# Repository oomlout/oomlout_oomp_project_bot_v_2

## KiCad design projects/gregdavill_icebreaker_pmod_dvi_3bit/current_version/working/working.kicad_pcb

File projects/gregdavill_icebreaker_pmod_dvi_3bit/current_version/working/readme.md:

# icebreaker_pmod
 
## summary 
* id: gregdavill_icebreaker_pmod_dvi_3bit
* user: gregdavill
* name: icebreaker_pmod
* board: dvi_3bit
* repo: https://github.com/gregdavill/icebreaker-pmod
* src_file_repo_kicad_pcb: dvi-3bit/v1.0a/dvi-3bit.kicad_pcb
* src_file_repo_kicad_pcb_link: https://github.com/gregdavill/icebreaker-pmod/tree/master/dvi-3bit/v1.0a/dvi-3bit.kicad_pcb

* src_file_repo_sch: dvi-3bit/v1.0a/dvi-3bit.sch
* src_file_repo_sch_link: https://github.com/gregdavill/icebreaker-pmod/tree/master/dvi-3bit/v1.0a/dvi-3bit.sch
* full details link: https://github.com/oomlout/oomlout_oomp_project_bot_v_2/tree/main/projects/gregdavill_icebreaker_pmod_dvi_3bit/current_version/working

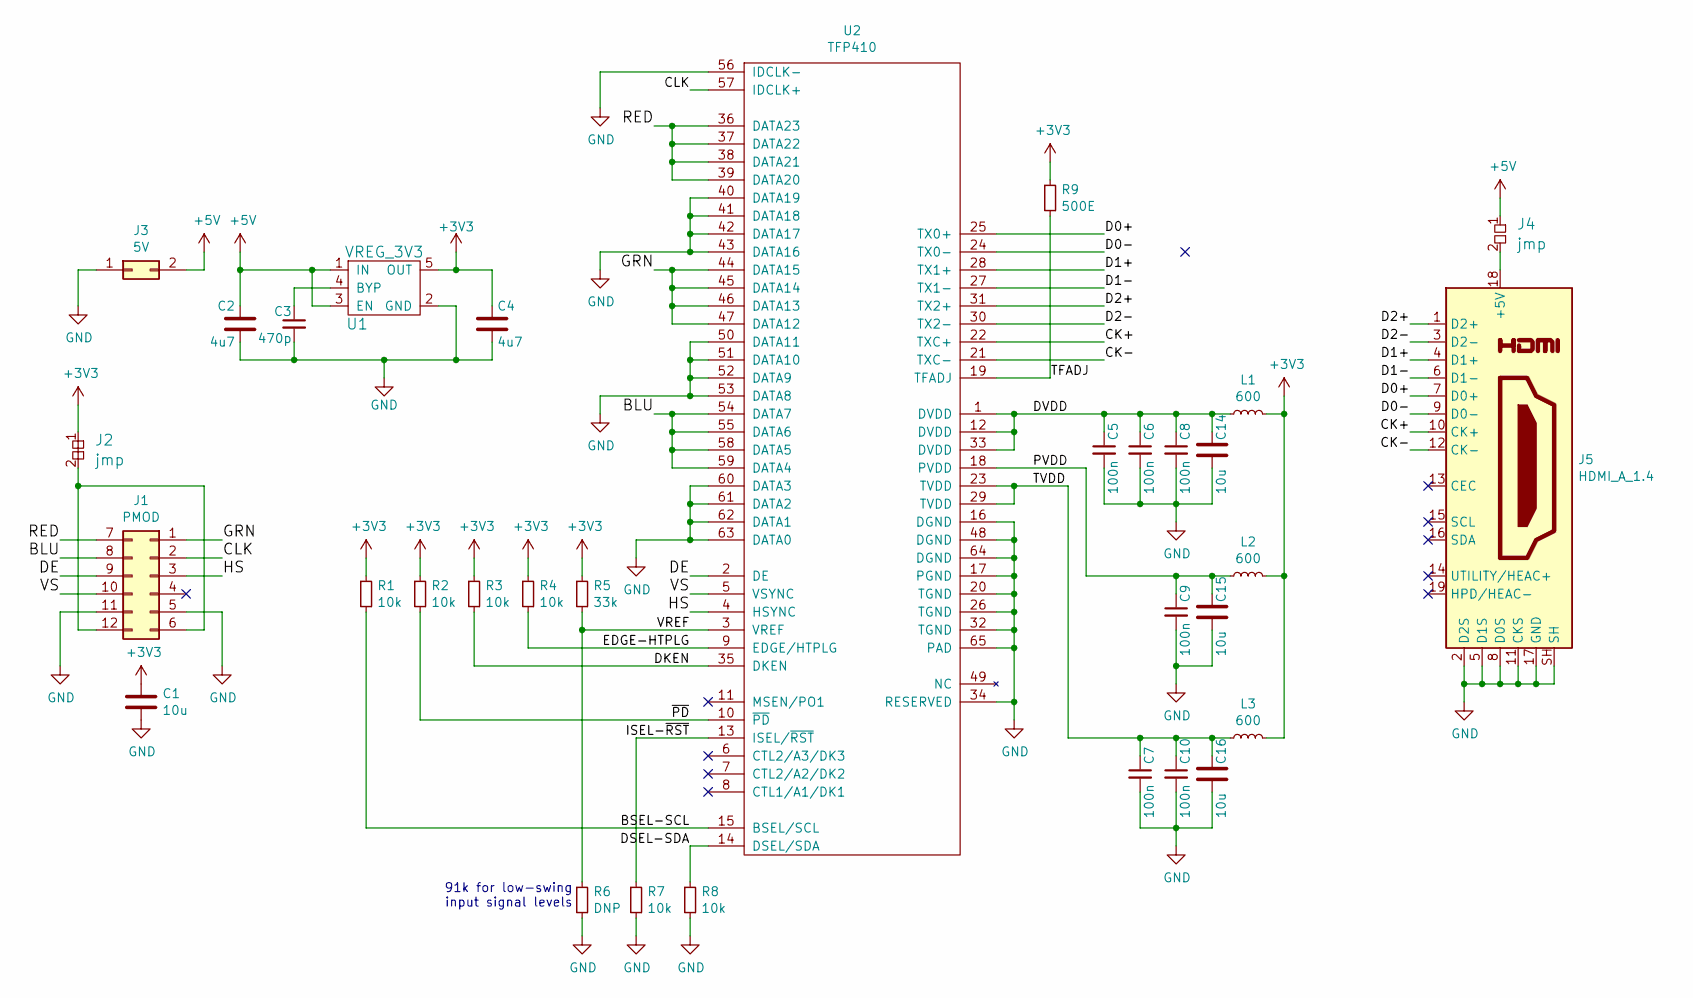
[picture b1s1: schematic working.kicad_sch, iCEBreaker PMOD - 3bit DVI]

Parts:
C1, C14, C15, C16: 10u; C_0603
C2, C4: 4u7; C_0603
C3: 470p; C_0402
C5, C6, C7, C8, C9, C10: 100n; C_0402
J1: PMOD; PMODHeader_2x06_P2.54mm_Horizontal
J2: jmp; J_NC_0603_30
J3: 5V; PinHeader_2x01_P2.54mm_Vertical
J4: jmp; J_0603
J5: HDMI_A_1.4; HDMI-10029449-111RLF
L1, L2, L3: 600; L_0402
R1, R2, R3, R4, R7, R8: 10k; R_0402
R5: 33k; R_0402
R6: DNP; R_0402
R9: 500E; R_0402
U1: VREG_3V3; SOT-23-5
U2: TFP410; TQFP-64-1EP_10x10mm_P0.5mm_EP5x5mm

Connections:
+3V3: C1.1, C4.1, J2.1, L1.1, L2.1, L3.1, R1.1, R2.1, R3.1, R4.1, R5.1, R9.1, U1.5 (OUT)
+5V: C2.1, J3.2, J4.1, U1.1 (IN), U1.3 (EN)
/BLU: J1.8, U2.54 (DATA7), U2.55 (DATA6), U2.58 (DATA5), U2.59 (DATA4)
/BSEL-SCL: R1.2, U2.15 (BSEL/SCL)
/CK+: J5.10 (CK+), U2.22 (TXC+)
/CK-: J5.12 (CK-), U2.21 (TXC-)
/CLK: J1.2, U2.57 (IDCLK+)
/D0+: J5.7 (D0+), U2.25 (TX0+)
/D0-: J5.9 (D0-), U2.24 (TX0-)
/D1+: J5.4 (D1+), U2.28 (TX1+)
/D1-: J5.6 (D1-), U2.27 (TX1-)
/D2+: J5.1 (D2+), U2.31 (TX2+)
/D2-: J5.3 (D2-), U2.30 (TX2-)
/DE: J1.9, U2.2 (DE)
/DKEN: R3.2, U2.35 (DKEN)
/DSEL-SDA: R8.1, U2.14 (DSEL/SDA)
/DVDD: C5.1, C6.1, C8.1, C14.1, L1.2, U2.1 (DVDD), U2.12 (DVDD), U2.33 (DVDD)
/EDGE-HTPLG: R4.2, U2.9 (EDGE/HTPLG)
/GRN: J1.1, U2.44 (DATA15), U2.45 (DATA14), U2.46 (DATA13), U2.47 (DATA12)
/HS: J1.3, U2.4 (HSYNC)
/ISEL-~RST: R7.1, U2.13 (ISEL/~RST)
/PVDD: C9.1, C15.1, L2.2, U2.18 (PVDD)
/RED: J1.7, U2.36 (DATA23), U2.37 (DATA22), U2.38 (DATA21), U2.39 (DATA20)
/TFADJ: R9.2, U2.19 (TFADJ)
/TVDD: C7.1, C10.1, C16.1, L3.2, U2.23 (TVDD), U2.29 (TVDD)
/VREF: R5.2, R6.1, U2.3 (VREF)
/VS: J1.10, U2.5 (VSYNC)
/~PD: R2.2, U2.10 (~PD)
GND: C1.2, C2.2, C3.2, C4.2, C5.2, C6.2, C7.2, C8.2, C9.2, C10.2, C14.2, C15.2, C16.2, J1.5, J1.11, J3.1, J5.2 (D2S), J5.5 (D1S), J5.8 (D0S), J5.11 (CKS), J5.17 (GND), J5.SH, R6.2, R7.2, R8.2, U1.2 (GND), U2.16 (DGND), U2.17 (PGND), U2.20 (TGND), U2.26 (TGND), U2.32 (TGND), U2.34 (RESERVED), U2.40 (DATA19), U2.41 (DATA18), U2.42 (DATA17), U2.43 (DATA16), U2.48 (DGND), U2.50 (DATA11), U2.51 (DATA10), U2.52 (DATA9), U2.53 (DATA8), U2.56 (IDCLK-), U2.60 (DATA3), U2.61 (DATA2), U2.62 (DATA1), U2.63 (DATA0), U2.64 (DGND), U2.65 (PAD)
unnamed: C3.1, U1.4 (BYP)
unnamed: J1.6, J1.12, J2.2
unnamed: J4.2, J5.18 (+5V)

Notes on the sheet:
91k for low-swing input signal levels

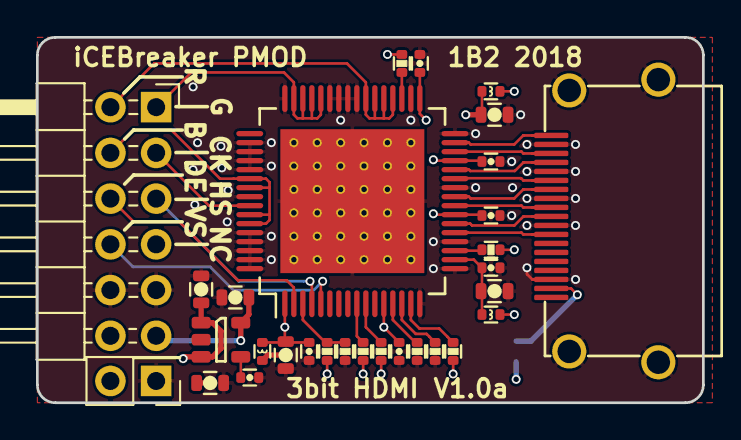
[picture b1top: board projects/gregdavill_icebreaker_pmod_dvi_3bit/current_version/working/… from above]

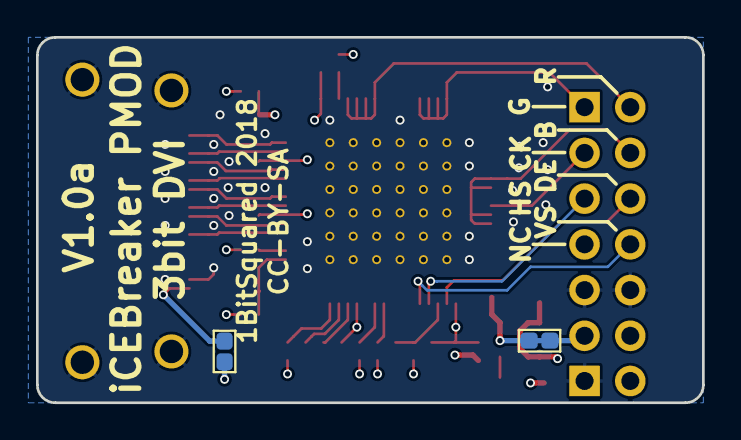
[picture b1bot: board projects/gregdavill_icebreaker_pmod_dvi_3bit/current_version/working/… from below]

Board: 4 copper layers, 37.0 x 20.3 mm, 32 parts (2 on the bottom side), 32 nets.

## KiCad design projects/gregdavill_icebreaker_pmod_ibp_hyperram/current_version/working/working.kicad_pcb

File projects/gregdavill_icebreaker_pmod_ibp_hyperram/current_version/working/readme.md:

# icebreaker_pmod
 
## summary 
* id: gregdavill_icebreaker_pmod_ibp_hyperram
* user: gregdavill
* name: icebreaker_pmod
* board: ibp_hyperram
* repo: https://github.com/gregdavill/icebreaker-pmod
* src_file_repo_kicad_pcb: hyperram/v1.0b/ibp-hyperram.kicad_pcb
* src_file_repo_kicad_pcb_link: https://github.com/gregdavill/icebreaker-pmod/tree/master/hyperram/v1.0b/ibp-hyperram.kicad_pcb

* src_file_repo_sch: hyperram/v1.0b/ibp-hyperram.sch
* src_file_repo_sch_link: https://github.com/gregdavill/icebreaker-pmod/tree/master/hyperram/v1.0b/ibp-hyperram.sch
* full details link: https://github.com/oomlout/oomlout_oomp_project_bot_v_2/tree/main/projects/gregdavill_icebreaker_pmod_ibp_hyperram/current_version/working

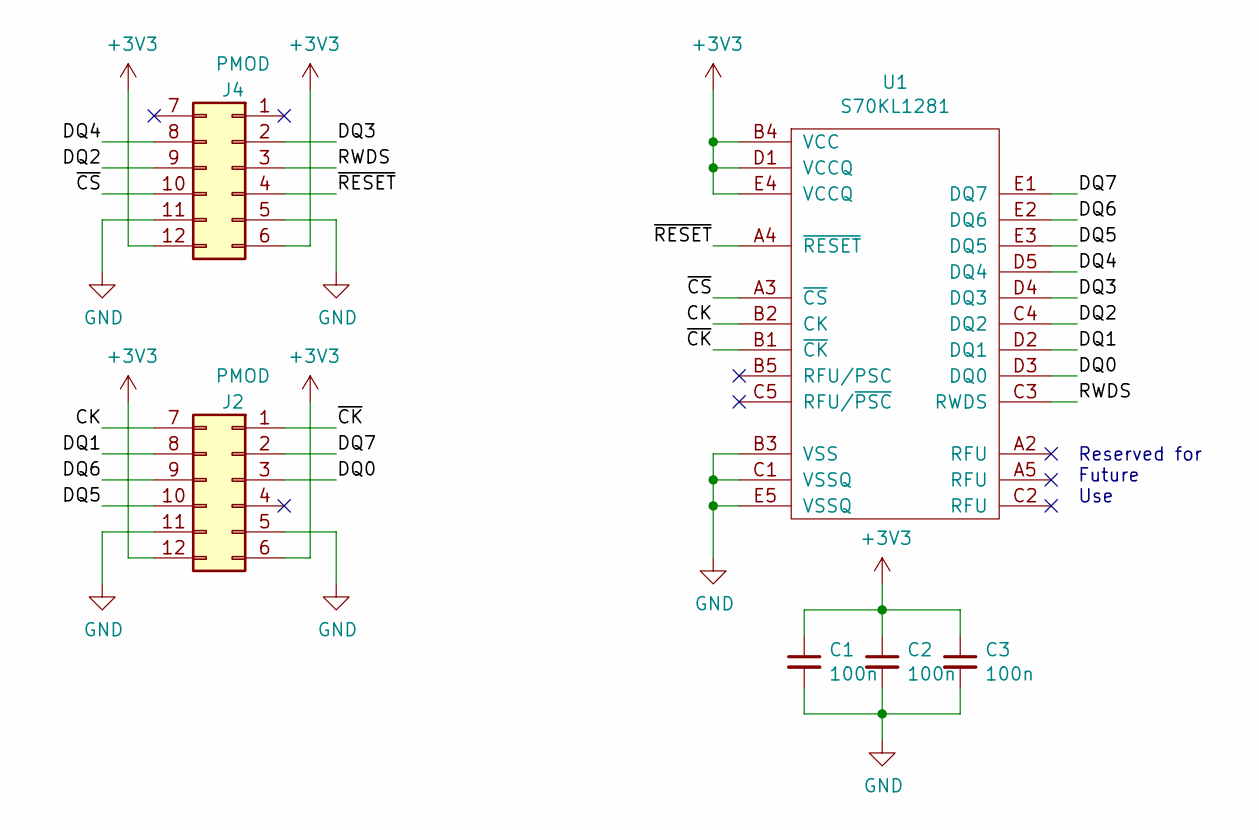
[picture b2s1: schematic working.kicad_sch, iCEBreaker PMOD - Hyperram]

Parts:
C1, C2, C3: 100n; C_0402
J2, J4: PMOD; PMODHeader_2x06_P2.54mm_Horizontal
U1: S70KL1281; BGA-24_5x5_6.0x8.0mm

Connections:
+3V3: C1.1, C2.1, C3.1, J2.6, J2.12, J4.6, J4.12, U1.B4 (VCC), U1.D1 (VCCQ), U1.E4 (VCCQ)
/CK: J2.7, U1.B2 (CK)
/DQ0: J2.3, U1.D3 (DQ0)
/DQ1: J2.8, U1.D2 (DQ1)
/DQ2: J4.9, U1.C4 (DQ2)
/DQ3: J4.2, U1.D4 (DQ3)
/DQ4: J4.8, U1.D5 (DQ4)
/DQ5: J2.10, U1.E3 (DQ5)
/DQ6: J2.9, U1.E2 (DQ6)
/DQ7: J2.2, U1.E1 (DQ7)
/RWDS: J4.3, U1.C3 (RWDS)
/~CK: J2.1, U1.B1 (~CK)
/~CS: J4.10, U1.A3 (~CS)
/~RESET: J4.4, U1.A4 (~RESET)
GND: C1.2, C2.2, C3.2, J2.5, J2.11, J4.5, J4.11, U1.B3 (VSS), U1.C1 (VSSQ), U1.E5 (VSSQ)

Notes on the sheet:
Reserved for Future Use

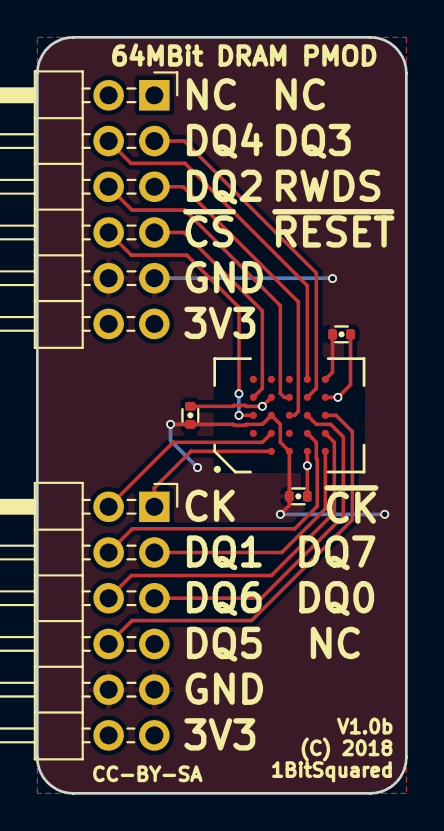
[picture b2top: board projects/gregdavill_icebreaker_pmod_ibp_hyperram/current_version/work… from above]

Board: 2 copper layers, 20.5 x 42.0 mm, 6 parts (0 on the bottom side), 15 nets.

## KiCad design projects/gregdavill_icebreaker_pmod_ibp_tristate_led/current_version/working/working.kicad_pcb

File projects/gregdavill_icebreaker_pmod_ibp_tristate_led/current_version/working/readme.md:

# icebreaker_pmod
 
## summary 
* id: gregdavill_icebreaker_pmod_ibp_tristate_led
* user: gregdavill
* name: icebreaker_pmod
* board: ibp_tristate_led
* repo: https://github.com/gregdavill/icebreaker-pmod
* src_file_repo_kicad_pcb: tristate-led/v1.0a/ibp-tristate-led.kicad_pcb
* src_file_repo_kicad_pcb_link: https://github.com/gregdavill/icebreaker-pmod/tree/master/tristate-led/v1.0a/ibp-tristate-led.kicad_pcb

* src_file_repo_sch: tristate-led/v1.0a/ibp-tristate-led.sch
* src_file_repo_sch_link: https://github.com/gregdavill/icebreaker-pmod/tree/master/tristate-led/v1.0a/ibp-tristate-led.sch
* full details link: https://github.com/oomlout/oomlout_oomp_project_bot_v_2/tree/main/projects/gregdavill_icebreaker_pmod_ibp_tristate_led/current_version/working

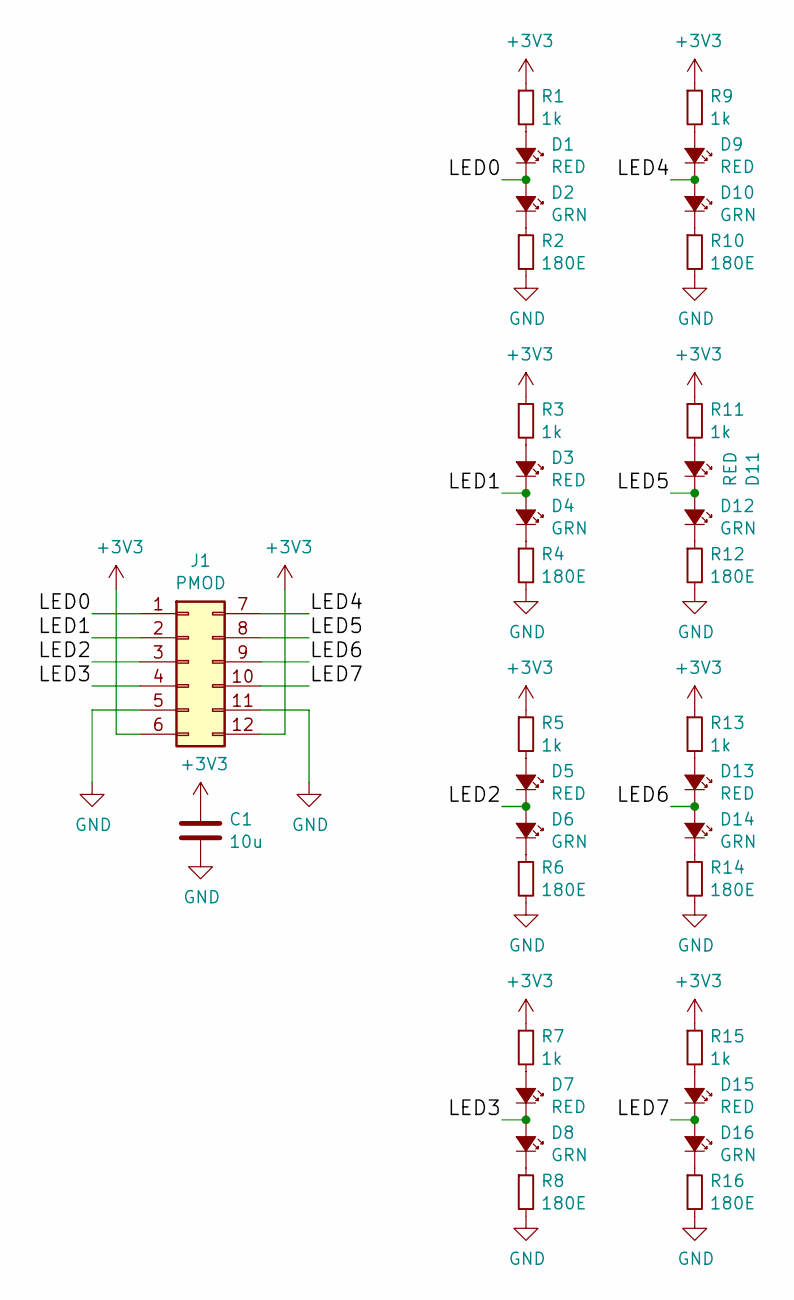
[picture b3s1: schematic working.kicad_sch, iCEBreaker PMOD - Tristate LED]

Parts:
C1: 10u; C_0603
D1, D3, D5, D7, D9, D11, D13, D15: RED; D_0603
D2, D4, D6, D8, D10, D12, D14, D16: GRN; D_0603
J1: PMOD; PMODHeader_2x06_P2.54mm_Horizontal
R1, R3, R5, R7, R9, R11, R13, R15: 1k; R_0402
R2, R4, R6, R8, R10, R12, R14, R16: 180E; R_0402

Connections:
+3V3: C1.1, J1.6, J1.12, R1.1, R3.1, R5.1, R7.1, R9.1, R11.1, R13.1, R15.1
/LED0: D1.C, D2.A, J1.1
/LED1: D3.C, D4.A, J1.2
/LED2: D5.C, D6.A, J1.3
/LED3: D7.C, D8.A, J1.4
/LED4: D9.C, D10.A, J1.7
/LED5: D11.C, D12.A, J1.8
/LED6: D13.C, D14.A, J1.9
/LED7: D15.C, D16.A, J1.10
GND: C1.2, J1.5, J1.11, R2.2, R4.2, R6.2, R8.2, R10.2, R12.2, R14.2, R16.2
unnamed: D1.A, R1.2
unnamed: D2.C, R2.1
unnamed: D3.A, R3.2
unnamed: D4.C, R4.1
unnamed: D5.A, R5.2
unnamed: D6.C, R6.1
unnamed: D7.A, R7.2
unnamed: D8.C, R8.1
unnamed: D9.A, R9.2
unnamed: D10.C, R10.1
unnamed: D11.A, R11.2
unnamed: D12.C, R12.1
unnamed: D13.A, R13.2
unnamed: D14.C, R14.1
unnamed: D15.A, R15.2
unnamed: D16.C, R16.1

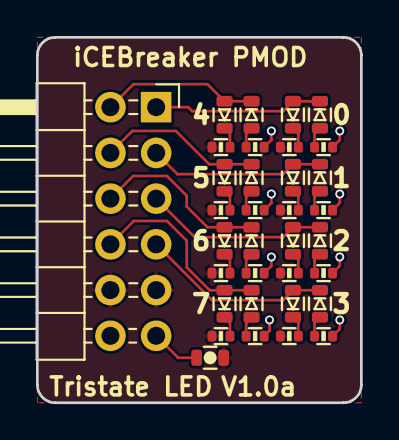
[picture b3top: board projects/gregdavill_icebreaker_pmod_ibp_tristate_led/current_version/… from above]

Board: 2 copper layers, 18.0 x 20.3 mm, 34 parts (0 on the bottom side), 26 nets.

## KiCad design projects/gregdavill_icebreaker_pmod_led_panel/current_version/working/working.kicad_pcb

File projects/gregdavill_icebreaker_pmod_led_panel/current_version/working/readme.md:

# icebreaker_pmod
 
## summary 
* id: gregdavill_icebreaker_pmod_led_panel
* user: gregdavill
* name: icebreaker_pmod
* board: led_panel
* repo: https://github.com/gregdavill/icebreaker-pmod
* src_file_repo_kicad_pcb: led-panel/v1.1a/led-panel.kicad_pcb
* src_file_repo_kicad_pcb_link: https://github.com/gregdavill/icebreaker-pmod/tree/master/led-panel/v1.1a/led-panel.kicad_pcb

* src_file_repo_sch: led-panel/v1.1a/led-panel.sch
* src_file_repo_sch_link: https://github.com/gregdavill/icebreaker-pmod/tree/master/led-panel/v1.1a/led-panel.sch
* full details link: https://github.com/oomlout/oomlout_oomp_project_bot_v_2/tree/main/projects/gregdavill_icebreaker_pmod_led_panel/current_version/working

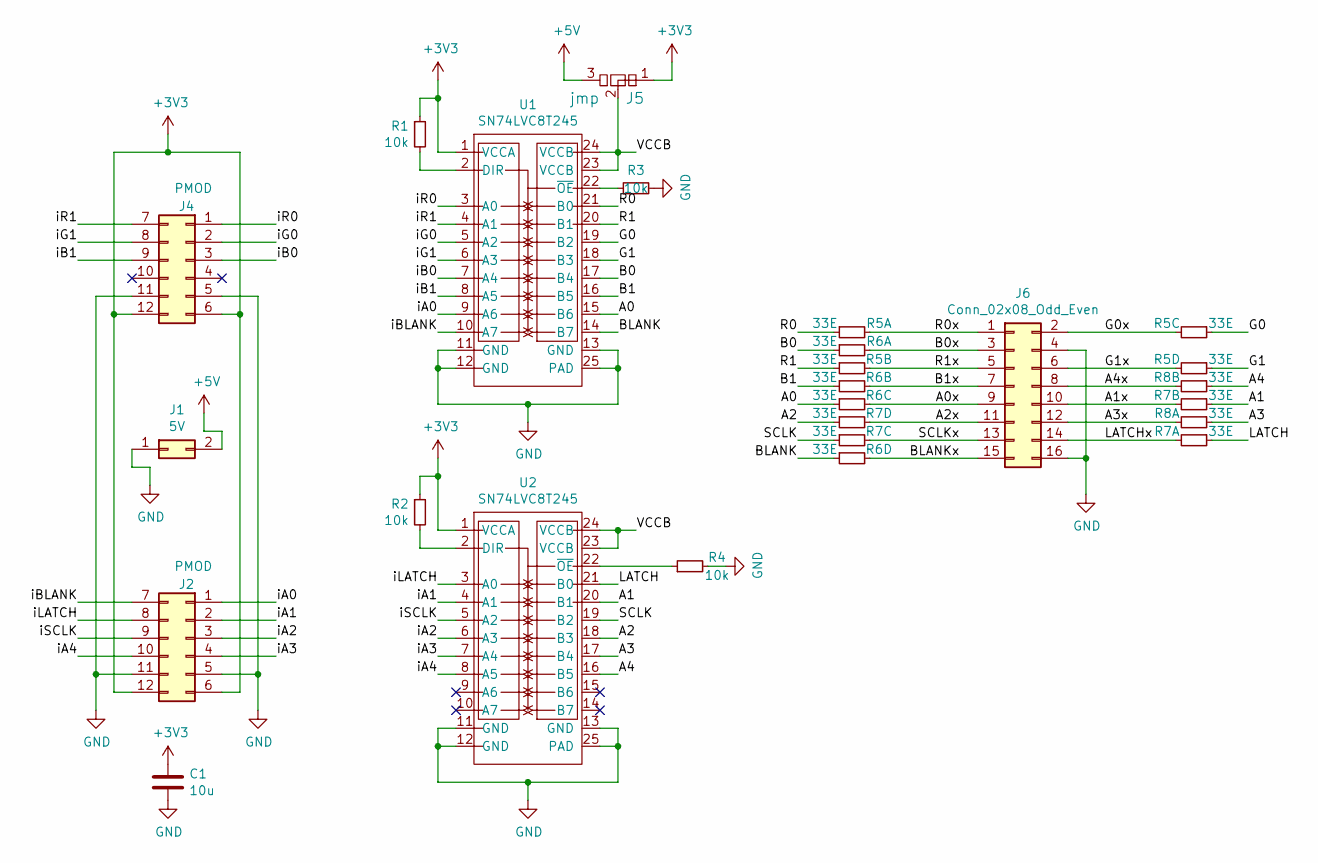
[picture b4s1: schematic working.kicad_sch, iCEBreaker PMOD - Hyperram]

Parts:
C1: 10u; C_0603
J1: 5V; PinHeader_2x01_P2.54mm_Vertical
J2, J4: PMOD; PMODHeader_2x06_P2.54mm_Horizontal
J5: jmp; J_NCNO_0903_30
J6: Conn_02x08_Odd_Even; PinHeader_2x08_P2.54mm_Vertical
R1, R2, R3, R4: 10k; R_0402
R5, R6, R7, R8: 33E; R_Array_Convex_4x0402
U1, U2: SN74LVC8T245; TSSOP-24_4.4x7.8mm_P0.65mm

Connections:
+3V3: C1.1, J2.6, J2.12, J4.6, J4.12, J5.1, R1.1, R2.1, U1.1 (VCCA), U2.1 (VCCA)
+5V: J1.2, J5.3
/A0: R6.5, U1.15 (B6)
/A0x: J6.9, R6.6
/A1: R7.3, U2.20 (B1)
/A1x: J6.10, R7.4
/A2: R7.7, U2.18 (B3)
/A2x: J6.11, R7.8
/A3: R8.1, U2.17 (B4)
/A3x: J6.12, R8.2
/A4: R8.3, U2.16 (B5)
/A4x: J6.8, R8.4
/B0: R6.1, U1.17 (B4)
/B0x: J6.3, R6.2
/B1: R6.3, U1.16 (B5)
/B1x: J6.7, R6.4
/BLANK: R6.7, U1.14 (B7)
/BLANKx: J6.15, R6.8
/G0: R5.5, U1.19 (B2)
/G0x: J6.2, R5.6
/G1: R5.7, U1.18 (B3)
/G1x: J6.6, R5.8
/LATCH: R7.1, U2.21 (B0)
/LATCHx: J6.14, R7.2
/R0: R5.1, U1.21 (B0)
/R0x: J6.1, R5.2
/R1: R5.3, U1.20 (B1)
/R1x: J6.5, R5.4
/SCLK: R7.5, U2.19 (B2)
/SCLKx: J6.13, R7.6
/VCCB: J5.2, U1.23 (VCCB), U1.24 (VCCB), U2.23 (VCCB), U2.24 (VCCB)
/iA0: J2.1, U1.9 (A6)
/iA1: J2.2, U2.4 (A1)
/iA2: J2.3, U2.6 (A3)
/iA3: J2.4, U2.7 (A4)
/iA4: J2.10, U2.8 (A5)
/iB0: J4.3, U1.7 (A4)
/iB1: J4.9, U1.8 (A5)
/iBLANK: J2.7, U1.10 (A7)
/iG0: J4.2, U1.5 (A2)
/iG1: J4.8, U1.6 (A3)
/iLATCH: J2.8, U2.3 (A0)
/iR0: J4.1, U1.3 (A0)
/iR1: J4.7, U1.4 (A1)
/iSCLK: J2.9, U2.5 (A2)
GND: C1.2, J1.1, J2.5, J2.11, J4.5, J4.11, J6.4, J6.16, R3.2, R4.2, U1.11 (GND), U1.12 (GND), U1.13 (GND), U1.25 (PAD), U2.11 (GND), U2.12 (GND), U2.13 (GND), U2.25 (PAD)
unnamed: R1.2, U1.2 (DIR)
unnamed: R2.2, U2.2 (DIR)
unnamed: R3.1, U1.22 (~OE)
unnamed: R4.1, U2.22 (~OE)

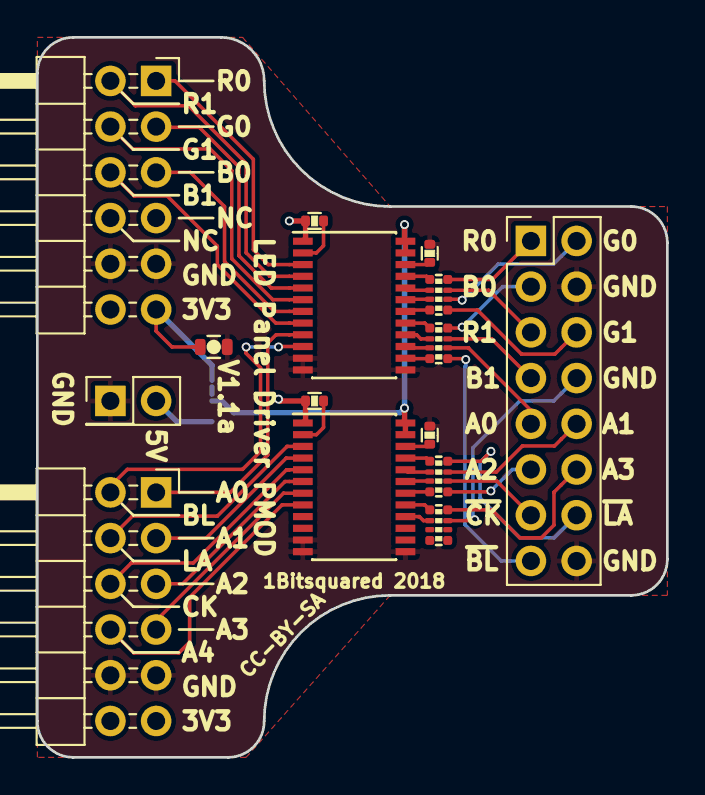
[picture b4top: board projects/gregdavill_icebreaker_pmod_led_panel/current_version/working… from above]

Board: 2 copper layers, 35.0 x 40.0 mm, 16 parts (1 on the bottom side), 50 nets.

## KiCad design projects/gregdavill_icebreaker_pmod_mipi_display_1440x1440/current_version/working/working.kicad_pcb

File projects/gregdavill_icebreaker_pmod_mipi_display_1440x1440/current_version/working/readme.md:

# icebreaker_pmod
 
## summary 
* id: gregdavill_icebreaker_pmod_mipi_display_1440x1440
* user: gregdavill
* name: icebreaker_pmod
* board: mipi_display_1440x1440
* repo: https://github.com/gregdavill/icebreaker-pmod
* src_file_repo_kicad_pcb: mipi-display-1440x1440/v0.1/mipi-display-1440x1440.kicad_pcb
* src_file_repo_kicad_pcb_link: https://github.com/gregdavill/icebreaker-pmod/tree/master/mipi-display-1440x1440/v0.1/mipi-display-1440x1440.kicad_pcb

* src_file_repo_sch: mipi-display-1440x1440/v0.1/mipi-display-1440x1440.sch
* src_file_repo_sch_link: https://github.com/gregdavill/icebreaker-pmod/tree/master/mipi-display-1440x1440/v0.1/mipi-display-1440x1440.sch
* full details link: https://github.com/oomlout/oomlout_oomp_project_bot_v_2/tree/main/projects/gregdavill_icebreaker_pmod_mipi_display_1440x1440/current_version/working

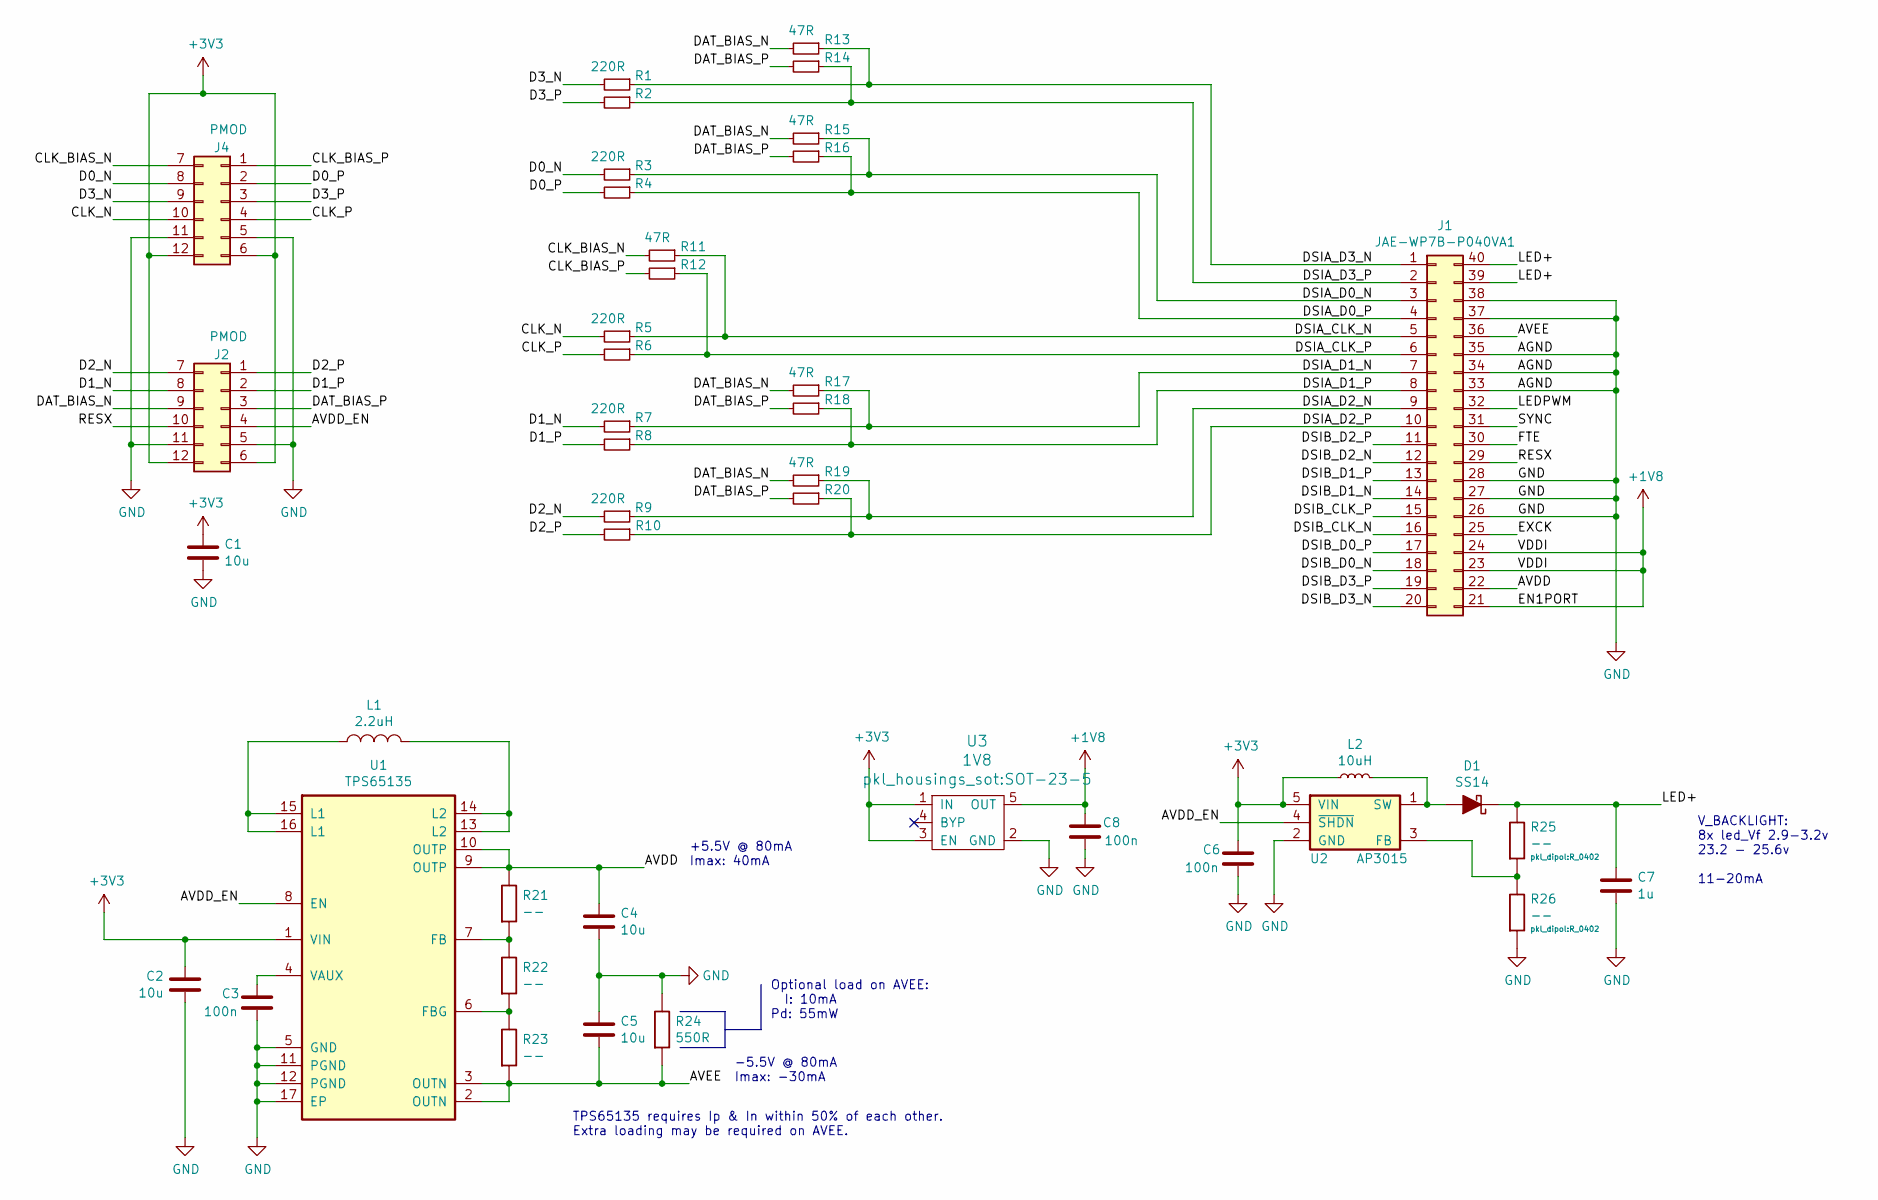
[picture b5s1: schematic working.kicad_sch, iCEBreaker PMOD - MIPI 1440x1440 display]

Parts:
C1, C2, C4, C5: 10u; C_0603
C3, C6, C8: 100n; C_0402
C7: 1u; C_0603
D1: SS14; L_0603
J1: JAE-WP7B-P040VA1
J2, J4: PMOD; PMODHeader_2x06_P2.54mm_Horizontal
L1: 2.2uH; L_Taiyo-Yuden_MD-3030
L2: 10uH; L_0603
R1, R2, R3, R4, R5, R6, R7, R8, R9, R10: 220R; R_0402
R11, R12, R13, R14, R15, R16, R17, R18, R19, R20: 47R; R_0402
R21, R22, R23, R25, R26: --; R_0402
R24: 550R; R_0603
U1: TPS65135; QFN-16-1EP_3x3mm_Pitch0.5mm
U2: AP3015; SOT-23-5
U3: 1V8; SOT-23-5

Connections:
+1V8: C8.1, J1.21, J1.23, J1.24, U3.5 (OUT)
+3V3: C1.1, C2.1, C6.1, J2.6, J2.12, J4.6, J4.12, L2.2, U1.1 (VIN), U2.5 (VIN), U3.1 (IN), U3.3 (EN)
/AVDD: C4.1, J1.22, R21.1, U1.9 (OUTP), U1.10 (OUTP)
/AVDD_EN: J2.4, U1.8 (EN), U2.4 (~SHDN)
/AVEE: C5.2, J1.36, R23.2, R24.2, U1.2 (OUTN), U1.3 (OUTN)
/CLK_BIAS_N: J4.7, R11.2
/CLK_BIAS_P: J4.1, R12.2
/CLK_N: J4.10, R5.2
/CLK_P: J4.4, R6.2
/D0_N: J4.8, R3.2
/D0_P: J4.2, R4.2
/D1_N: J2.8, R7.2
/D1_P: J2.2, R8.2
/D2_N: J2.7, R9.2
/D2_P: J2.1, R10.2
/D3_N: J4.9, R1.2
/D3_P: J4.3, R2.2
/DAT_BIAS_N: J2.9, R13.2, R15.2, R17.2, R19.2
/DAT_BIAS_P: J2.3, R14.2, R16.2, R18.2, R20.2
/DSIA_CLK_N: J1.5, R5.1, R11.1
/DSIA_CLK_P: J1.6, R6.1, R12.1
/DSIA_D0_N: J1.3, R3.1, R15.1
/DSIA_D0_P: J1.4, R4.1, R16.1
/DSIA_D1_N: J1.7, R7.1, R17.1
/DSIA_D1_P: J1.8, R8.1, R18.1
/DSIA_D2_N: J1.9, R9.1, R19.1
/DSIA_D2_P: J1.10, R10.1, R20.1
/DSIA_D3_N: J1.1, R1.1, R13.1
/DSIA_D3_P: J1.2, R2.1, R14.1
/DSIB_CLK_N: J1.16
/DSIB_CLK_P: J1.15
/DSIB_D0_N: J1.18
/DSIB_D0_P: J1.17
/DSIB_D1_N: J1.14
/DSIB_D1_P: J1.13
/DSIB_D2_N: J1.12
/DSIB_D2_P: J1.11
/DSIB_D3_N: J1.20
/DSIB_D3_P: J1.19
/EXCK: J1.25
/FTE: J1.30
/LED+: C7.1, D1.1 (K), J1.39, J1.40, R25.1
/LEDPWM: J1.32
/RESX: J1.29, J2.10
/SYNC: J1.31
GND: C1.2, C2.2, C3.2, C4.2, C5.1, C6.2, C7.2, C8.2, J1.26, J1.27, J1.28, J1.33, J1.34, J1.35, J1.37, J1.38, J2.5, J2.11, J4.5, J4.11, R24.1, R26.2, U1.5 (GND), U1.11 (PGND), U1.12 (PGND), U1.17 (EP), U2.2 (GND), U3.2 (GND)
unnamed: C3.1, U1.4 (VAUX)
unnamed: D1.2 (A), L2.1, U2.1 (SW)
unnamed: L1.1, U1.15 (L1), U1.16 (L1)
unnamed: L1.2, U1.13 (L2), U1.14 (L2)
unnamed: R21.2, R22.1, U1.7 (FB)
unnamed: R22.2, R23.1, U1.6 (FBG)
unnamed: R25.2, R26.1, U2.3 (FB)

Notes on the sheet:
TPS65135 requires Ip & In within 50% of each other. Extra loading may be required on AVEE.
V_BACKLIGHT: 8x led_Vf 2.9-3.2v 23.2 - 25.6v 11-20mA
+5.5V @ 80mA Imax: 40mA
-5.5V @ 80mA Imax: -30mA
Optional load on AVEE: I: 10mA Pd: 55mW

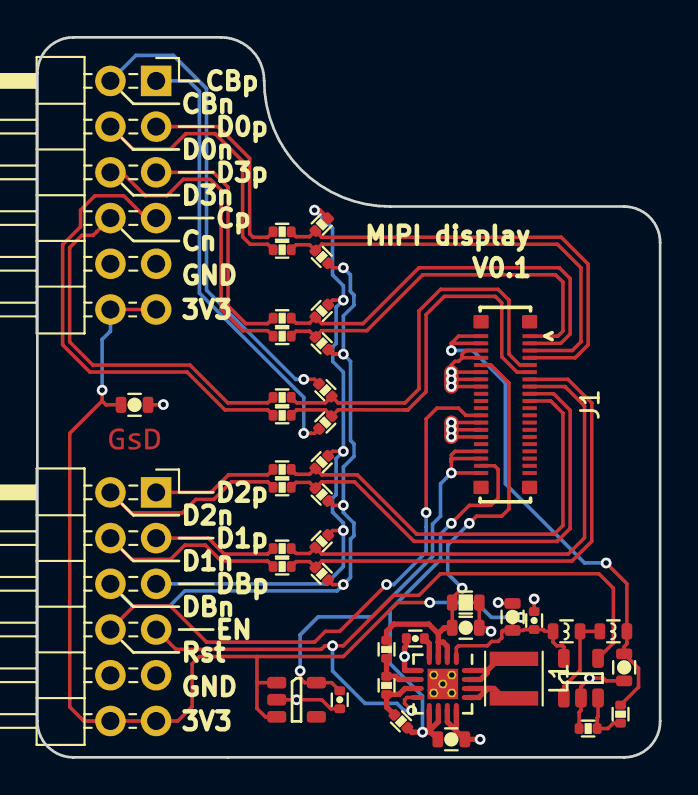
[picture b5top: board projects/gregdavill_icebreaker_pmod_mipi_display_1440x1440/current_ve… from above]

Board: 2 copper layers, 34.6 x 40.0 mm, 43 parts (0 on the bottom side), 39 nets.

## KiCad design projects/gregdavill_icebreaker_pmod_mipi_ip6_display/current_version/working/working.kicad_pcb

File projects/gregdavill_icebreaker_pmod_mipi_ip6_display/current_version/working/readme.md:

# icebreaker_pmod
 
## summary 
* id: gregdavill_icebreaker_pmod_mipi_ip6_display
* user: gregdavill
* name: icebreaker_pmod
* board: mipi_ip6_display
* repo: https://github.com/gregdavill/icebreaker-pmod
* src_file_repo_kicad_pcb: mipi-ip6-display/v0.1/mipi-ip6-display.kicad_pcb
* src_file_repo_kicad_pcb_link: https://github.com/gregdavill/icebreaker-pmod/tree/master/mipi-ip6-display/v0.1/mipi-ip6-display.kicad_pcb

* src_file_repo_sch: mipi-ip6-display/v0.1/mipi-ip6-display.sch
* src_file_repo_sch_link: https://github.com/gregdavill/icebreaker-pmod/tree/master/mipi-ip6-display/v0.1/mipi-ip6-display.sch
* full details link: https://github.com/oomlout/oomlout_oomp_project_bot_v_2/tree/main/projects/gregdavill_icebreaker_pmod_mipi_ip6_display/current_version/working

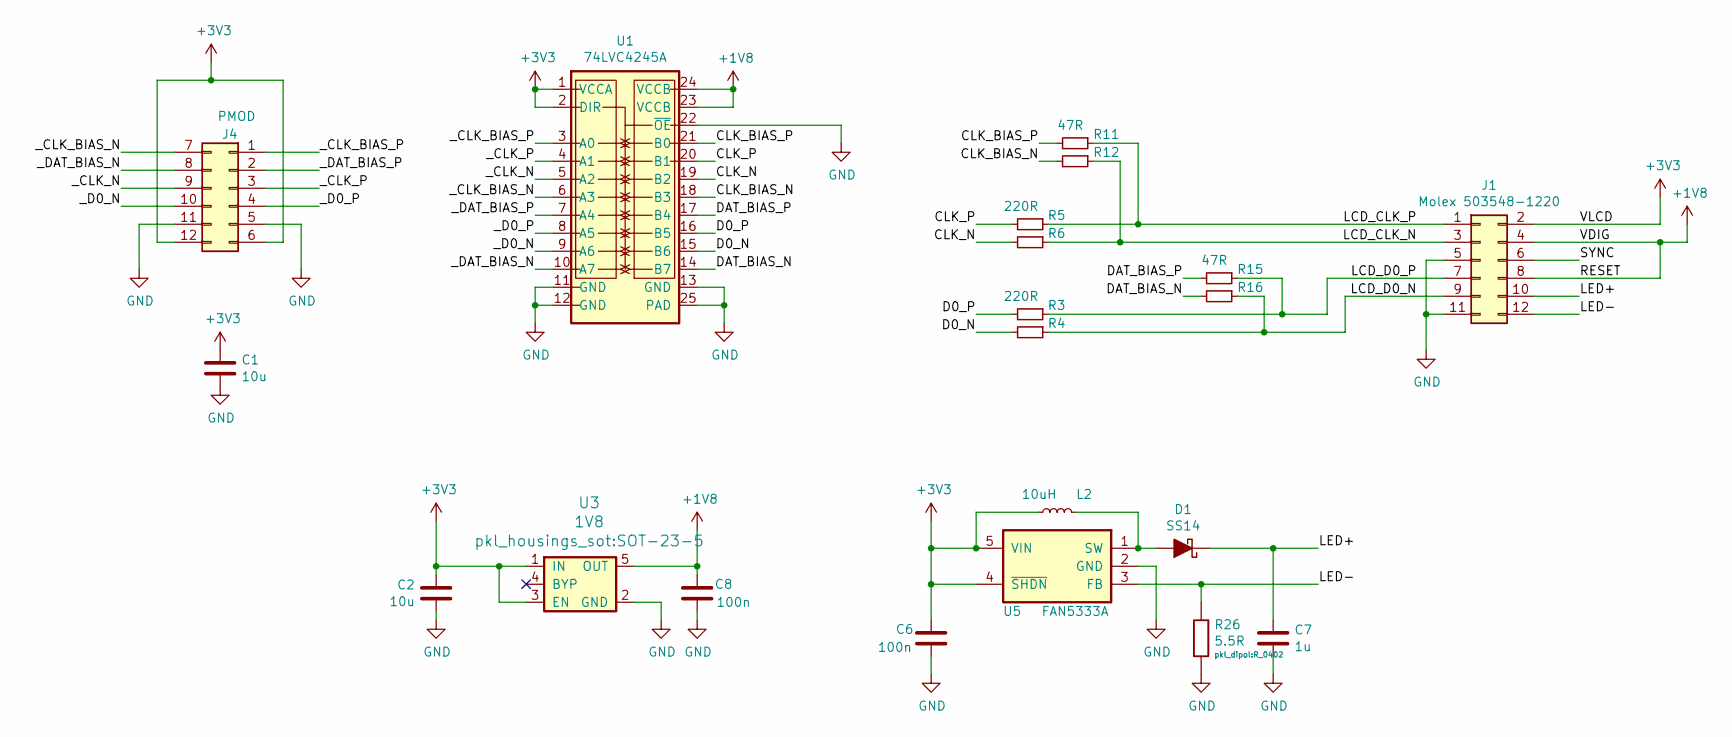
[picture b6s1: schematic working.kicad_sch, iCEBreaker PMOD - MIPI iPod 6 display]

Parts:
C1, C2: 10u; C_0603
C6, C8: 100n; C_0402
C7: 1u; C_0603
D1: SS14; L_0603
J1: Molex 503548-1220
J4: PMOD; PMODHeader_2x06_P2.54mm_Horizontal
L2: 10uH; L_0603
R3, R4, R5, R6: 220R; R_0402
R11, R12, R15, R16: 47R; R_0402
R26: 5.5R; R_0402
U1: 74LVC4245A; DHVQFN-24-1EP_5.5x3.5mm_P0.5mm
U3: 1V8; SOT-23-5
U5: FAN5333A; SOT-23-5

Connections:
+1V8: C8.1, J1.4, J1.8, U1.23 (VCCB), U1.24 (VCCB), U3.5 (OUT)
+3V3: C1.1, C2.1, C6.1, J1.2, J4.6, J4.12, L2.2, U1.1 (VCCA), U1.2 (DIR), U3.1 (IN), U3.3 (EN), U5.4 (~SHDN), U5.5 (VIN)
/CLK_BIAS_N: R12.2, U1.18 (B3)
/CLK_BIAS_P: R11.2, U1.21 (B0)
/CLK_N: R6.2, U1.19 (B2)
/CLK_P: R5.2, U1.20 (B1)
/D0_N: R4.2, U1.15 (B6)
/D0_P: R3.2, U1.16 (B5)
/DAT_BIAS_N: R16.2, U1.14 (B7)
/DAT_BIAS_P: R15.2, U1.17 (B4)
/LCD_CLK_N: J1.3, R6.1, R12.1
/LCD_CLK_P: J1.1, R5.1, R11.1
/LCD_D0_N: J1.9, R4.1, R16.1
/LCD_D0_P: J1.7, R3.1, R15.1
/LED+: C7.1, D1.1 (K), J1.10
/LED-: J1.12, R26.1, U5.3 (FB)
/SYNC: J1.6
/_CLK_BIAS_N: J4.7, U1.6 (A3)
/_CLK_BIAS_P: J4.1, U1.3 (A0)
/_CLK_N: J4.9, U1.5 (A2)
/_CLK_P: J4.3, U1.4 (A1)
/_D0_N: J4.10, U1.9 (A6)
/_D0_P: J4.4, U1.8 (A5)
/_DAT_BIAS_N: J4.8, U1.10 (A7)
/_DAT_BIAS_P: J4.2, U1.7 (A4)
GND: C1.2, C2.2, C6.2, C7.2, C8.2, J1.5, J1.11, J4.5, J4.11, R26.2, U1.11 (GND), U1.12 (GND), U1.13 (GND), U1.22 (~OE), U1.25 (PAD), U3.2 (GND), U5.2 (GND)
unnamed: D1.2 (A), L2.1, U5.1 (SW)

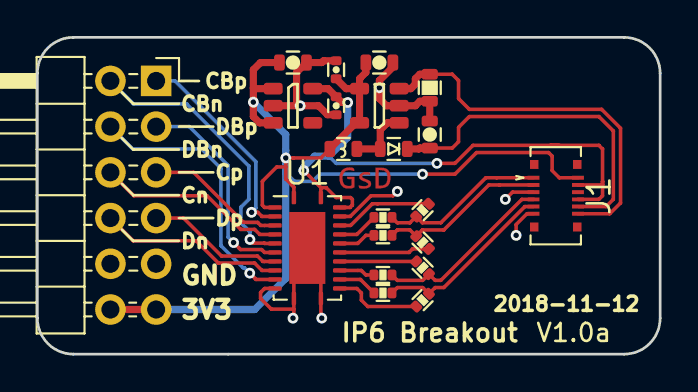
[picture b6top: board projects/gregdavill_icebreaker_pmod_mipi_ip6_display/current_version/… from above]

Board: 2 copper layers, 34.6 x 17.6 mm, 21 parts (0 on the bottom side), 26 nets.

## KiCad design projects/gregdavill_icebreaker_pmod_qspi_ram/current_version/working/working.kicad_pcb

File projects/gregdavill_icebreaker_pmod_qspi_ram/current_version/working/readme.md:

# icebreaker_pmod
 
## summary 
* id: gregdavill_icebreaker_pmod_qspi_ram
* user: gregdavill
* name: icebreaker_pmod
* board: qspi_ram
* repo: https://github.com/gregdavill/icebreaker-pmod
* src_file_repo_kicad_pcb: qspi-ram/v1.0a/qspi-ram.kicad_pcb
* src_file_repo_kicad_pcb_link: https://github.com/gregdavill/icebreaker-pmod/tree/master/qspi-ram/v1.0a/qspi-ram.kicad_pcb

* src_file_repo_sch: qspi-ram/v1.0a/qspi-ram.sch
* src_file_repo_sch_link: https://github.com/gregdavill/icebreaker-pmod/tree/master/qspi-ram/v1.0a/qspi-ram.sch
* full details link: https://github.com/oomlout/oomlout_oomp_project_bot_v_2/tree/main/projects/gregdavill_icebreaker_pmod_qspi_ram/current_version/working

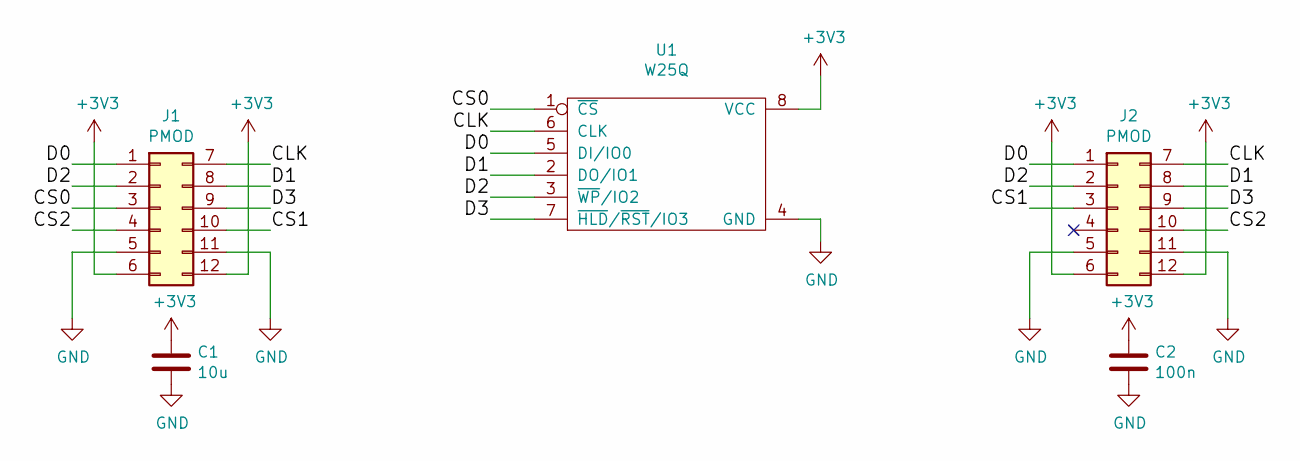
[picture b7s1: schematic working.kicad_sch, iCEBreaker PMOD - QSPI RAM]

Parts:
C1: 10u; C_0603
C2: 100n; C_0603
J1, J2: PMOD; PMODHeader_2x06_P2.54mm_Horizontal
U1: W25Q; SOIC-8_5.3x5.3mm_Pitch1.27mm

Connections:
+3V3: C1.1, C2.1, J1.6, J1.12, J2.6, J2.12, U1.8 (VCC)
/CLK: J1.7, J2.7, U1.6 (CLK)
/CS0: J1.3, U1.1 (~CS)
/CS1: J1.10, J2.3
/CS2: J1.4, J2.10
/D0: J1.1, J2.1, U1.5 (DI/IO0)
/D1: J1.8, J2.8, U1.2 (DO/IO1)
/D2: J1.2, J2.2, U1.3 (~WP/IO2)
/D3: J1.9, J2.9, U1.7 (~HLD/~RST/IO3)
GND: C1.2, C2.2, J1.5, J1.11, J2.5, J2.11, U1.4 (GND)

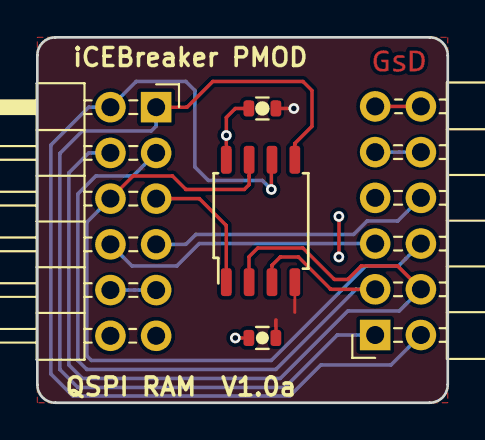
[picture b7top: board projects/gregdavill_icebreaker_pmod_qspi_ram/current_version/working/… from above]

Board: 2 copper layers, 22.8 x 20.3 mm, 5 parts (0 on the bottom side), 10 nets.

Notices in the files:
projects/gregdavill_icebreaker_pmod_dvi_3bit/current_version/working/working.kicad_pcb:
(C) 2018 Piotr Esden-Tempski
(C) 2018 1BitSquared
License: CC-BY-SA V4.0
CC-BY-SA
projects/gregdavill_icebreaker_pmod_ibp_hyperram/current_version/working/working.kicad_pcb:
License: CC-BY-SA 4.0
(C) 2018
projects/gregdavill_icebreaker_pmod_ibp_tristate_led/current_version/working/working.kicad_pcb:
CC-BY-SA 4.0
projects/gregdavill_icebreaker_pmod_qspi_ram/current_version/working/working.kicad_pcb:
(C) 2018 Greg Davill
